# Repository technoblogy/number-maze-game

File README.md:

# Number Maze Game
A handheld game that displays logic mazes you have to solve by pressing the buttons.

For the original version see: <http://www.technoblogy.com/show?45JT>.

For the updated version, with additional harder mazes, see: <http://www.technoblogy.com/show?48BN>.

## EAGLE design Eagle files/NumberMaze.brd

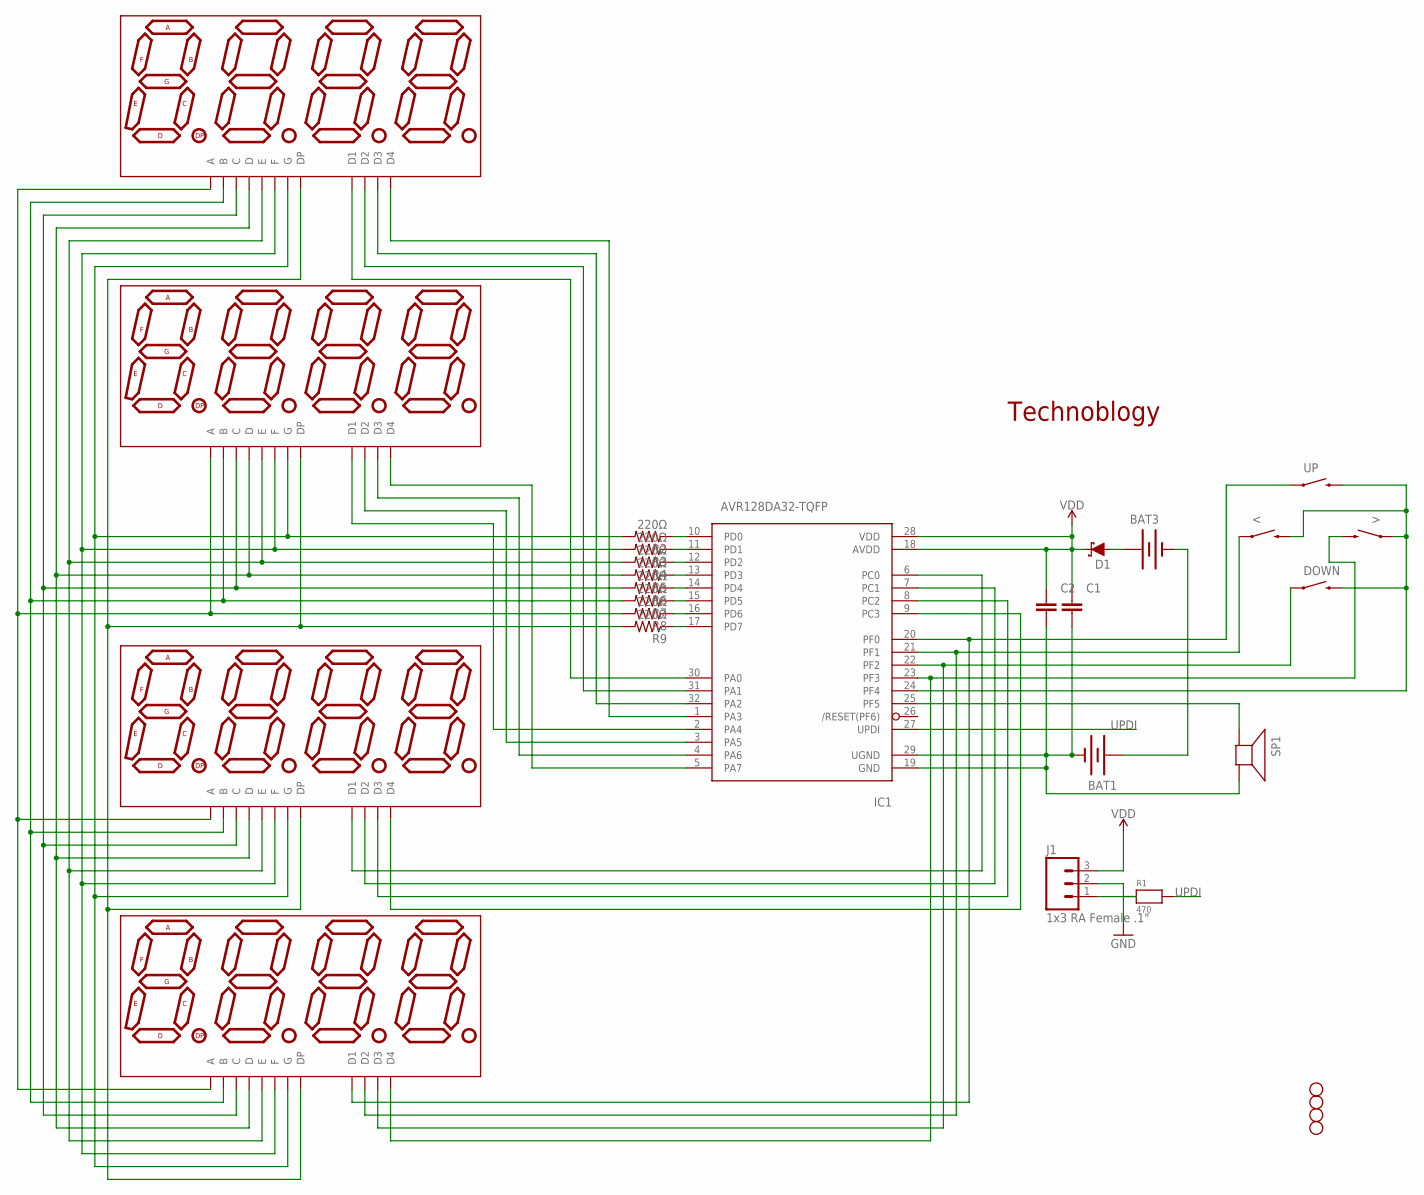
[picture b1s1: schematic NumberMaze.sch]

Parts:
<: SWITCH-MOMENTARY-2PTH; TACTILE-PTH
>: SWITCH-MOMENTARY-2PTH; TACTILE-PTH
BAT1, BAT3: BATTERYAA-KIT; BATTERY-AA-KIT
C1, C2: 100n; 0805
D1: 3A/10V/280mV; SOD-323
DISP1, DISP2, DISP3, DISP4: KYX-2381
DOWN: SWITCH-MOMENTARY-2PTH; TACTILE-PTH
IC1: AVR128DA32-TQFP; TQFP32-08
J1: 1x3 RA Female .1"; 1X03_SMD_RA_FEMALE
JP1, JP2, JP4, JP5: STAND-OFF
R1: 470; _0805MP
R2, R3, R4, R5, R6, R7, R8, R9: 220Ω; 0805
SP1: SPEAKER/AL60P; AL60P
UP: SWITCH-MOMENTARY-2PTH; TACTILE-PTH

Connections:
GND: BAT1.GND@1 (-), C1.2, C2.2, IC1.19 (GND), IC1.29 (UGND), J1.2, SP1.2 (-)
unnamed: DISP1.11 (A), DISP2.11 (A), DISP3.11 (A), DISP4.11 (A), R8.2
unnamed: DISP1.7 (B), DISP2.7 (B), DISP3.7 (B), DISP4.7 (B), R7.2
unnamed: DISP1.4 (C), DISP2.4 (C), DISP3.4 (C), DISP4.4 (C), R6.2
unnamed: DISP1.2 (D), DISP2.2 (D), DISP3.2 (D), DISP4.2 (D), R5.2
unnamed: DISP1.1 (E), DISP2.1 (E), DISP3.1 (E), DISP4.1 (E), R4.2
unnamed: DISP1.10 (F), DISP2.10 (F), DISP3.10 (F), DISP4.10 (F), R3.2
unnamed: DISP1.5 (G), DISP2.5 (G), DISP3.5 (G), DISP4.5 (G), R2.2
unnamed: DISP1.3 (DP), DISP2.3 (DP), DISP3.3 (DP), DISP4.3 (DP), R9.2
unnamed: IC1.17 (PD7), R9.1
unnamed: IC1.16 (PD6), R8.1
unnamed: IC1.15 (PD5), R7.1
unnamed: IC1.14 (PD4), R6.1
unnamed: IC1.13 (PD3), R5.1
unnamed: IC1.12 (PD2), R4.1
unnamed: IC1.11 (PD1), R3.1
unnamed: IC1.10 (PD0), R2.1
unnamed: BAT3.PWR@1 (+), D1.A
unnamed: IC1.25 (PF5), SP1.1 (+)
unnamed: DISP3.9 (D2), IC1.7 (PC1)
unnamed: BAT1.PWR@1 (+), BAT3.GND@1 (-)
unnamed: DISP1.6 (D4), IC1.1 (PA3)
unnamed: DISP3.6 (D4), IC1.9 (PC3)
unnamed: DISP1.12 (D1), IC1.30 (PA0)
unnamed: DISP1.9 (D2), IC1.31 (PA1)
unnamed: DISP1.8 (D3), IC1.32 (PA2)
unnamed: <.3 (2), >.1, DOWN.3 (2), IC1.24 (PF4), UP.3 (2)
unnamed: DISP2.6 (D4), IC1.5 (PA7)
unnamed: DISP2.8 (D3), IC1.4 (PA6)
unnamed: DISP4.12 (D1), IC1.20 (PF0), UP.1
unnamed: <.1, DISP4.9 (D2), IC1.21 (PF1)
unnamed: DISP4.8 (D3), DOWN.1, IC1.22 (PF2)
unnamed: >.3 (2), DISP4.6 (D4), IC1.23 (PF3)
unnamed: DISP3.8 (D3), IC1.8 (PC2)
unnamed: J1.1, R1.1
unnamed: DISP3.12 (D1), IC1.6 (PC0)
unnamed: DISP2.9 (D2), IC1.3 (PA5)
unnamed: DISP2.12 (D1), IC1.2 (PA4)
UPDI: IC1.27 (UPDI), R1.2
VDD: C1.1, C2.1, D1.C, IC1.18 (AVDD), IC1.28 (VDD), J1.3

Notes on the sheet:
Technoblogy

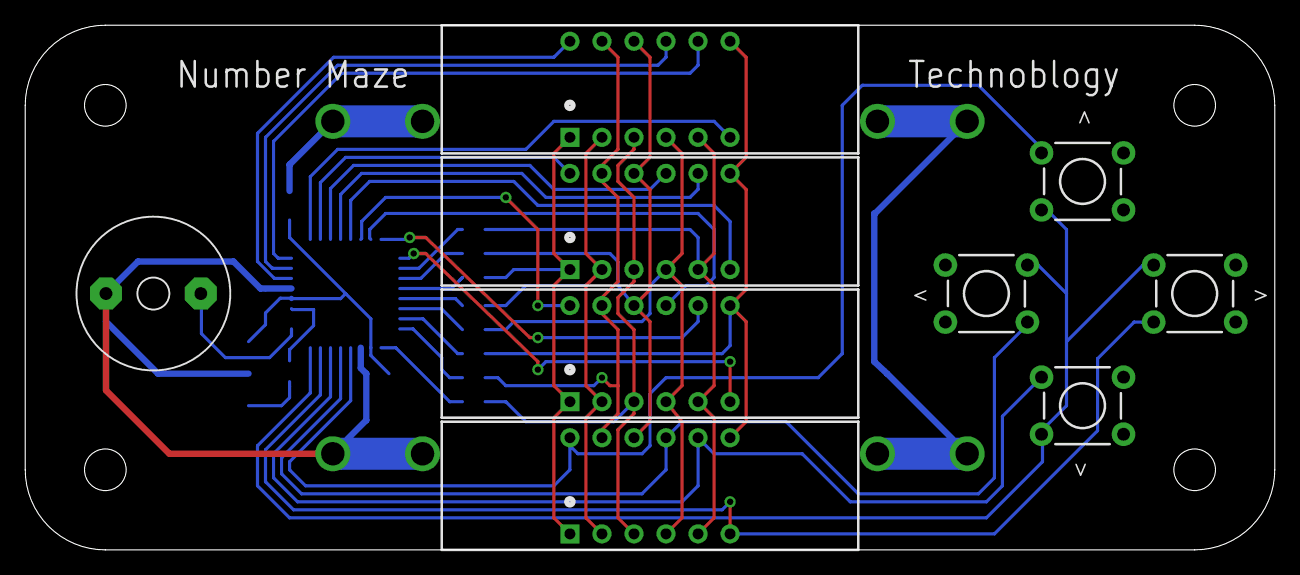
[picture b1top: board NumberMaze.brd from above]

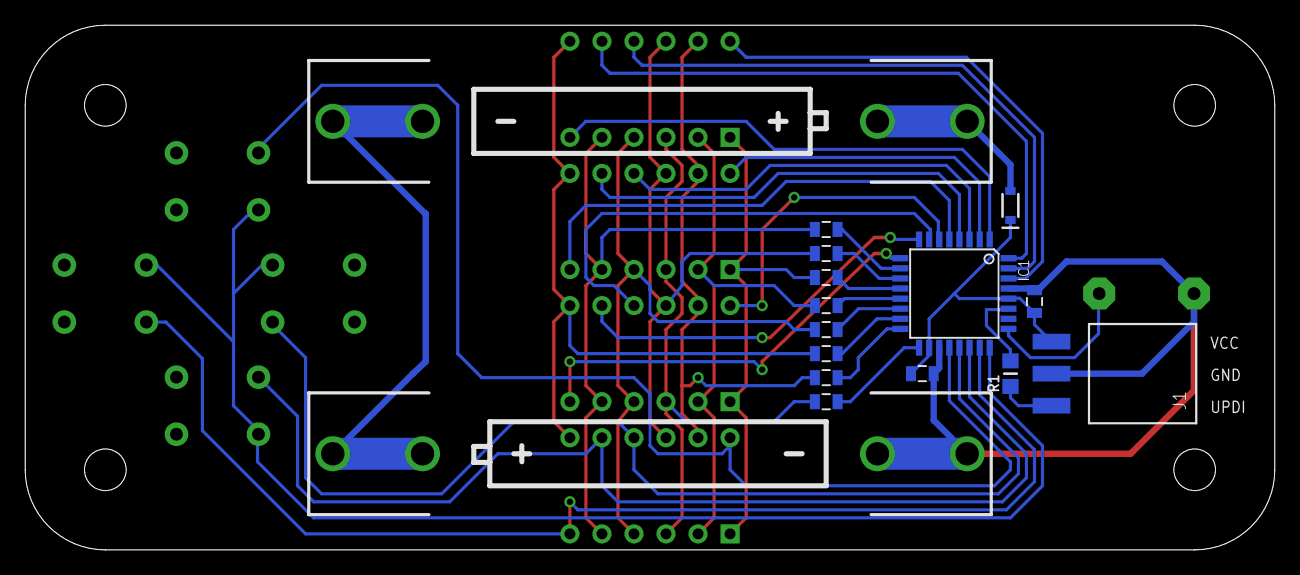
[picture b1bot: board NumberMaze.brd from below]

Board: 2 copper layers, 99.1 x 41.6 mm, 29 parts (16 on the bottom side), 40 nets.

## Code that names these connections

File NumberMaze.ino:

/* Number Maze Game - see http://www.technoblogy.com/show?45JT

   David Johnson-Davies - www.technoblogy.com - 21st December 2022
   AVR128DA32 or ATmega4808 @ 4 MHz (internal oscillator; BOD disabled)
   
   CC BY 4.0
   Licensed under a Creative Commons Attribution 4.0 International license: 
   http://creativecommons.org/licenses/by/4.0/
*/

#include <avr/sleep.h>

#if defined(__AVR_ATmegax08__)
#define TCB_CLKSEL_DIV1_gc TCB_CLKSEL_CLKDIV1_gc
#endif

// Seven segment displays

// Cathodes, Arduino pin numbers
uint8_t cathode[16] = { 0, 1, 2, 3, 4, 5, 6, 7, 8, 9, 10, 11, 20, 21, 22, 23 };

// Translation tables
uint8_t symbol[]  = { '0',  '1',  '2',  '3',  '4',  '5',  '6',  '7',  '8',  '9',  
                      ' ',  'H',  'P', 'L',  'A',  'Y',   'n',  'o',  0xff };
uint8_t segment[] = { 0x7e, 0x30, 0x6d, 0x79, 0x33, 0x5b, 0x5f, 0x70, 0x7f, 0x7b,
                      0x00, 0x37, 0x67, 0x0e, 0x77, 0x3b, 0x15, 0x1d, 0xff };

// Mazes
const int TotalMazes = 12;

uint8_t mazes[TotalMazes][17] = {
  "201111232221212H", // 7 8+5
  "3212122112H21213", // 7 7+4
  "121213122132213H", // 8 9+3
  "221121112222111H", // 8 9b+3
  "131212131131232H", // 9 9+2
  "112213123122112H", // 9 10+4
  "1313213221H22332", // 10 8+3
  "231111333113332H", // 10 9+0
  "3131221212H33133", // 10 9+2
  "222231131321112H", // 10 10+1
  "223121212121112H", // 11 8+3
  "212331013310132H"  // 11 8b+0
};

// Number of steps in each maze
uint8_t steps[TotalMazes] = { 7, 7, 8, 8, 9, 9, 10, 10, 10, 10, 11, 11 }; 

// Intro screen
uint8_t intro[17] = { "    PLAYno 1    " };

// Globals
int Maze = 0;
uint8_t *Buffer = intro;
volatile uint8_t Sound = 0;
enum sounds { NONE, HORIZONTAL, VERTICAL, UNDO, SOLVED };
volatile uint8_t Player = 16;

// Buttons **********************************************

void SetupButtons () {
  PORTF.PIN4CTRL = PORT_PULLUPEN_bm;                       // PF4 input pullup
}

ISR(PORTF_PORT_vect) {
  PORTF.INTFLAGS = PIN4_bm;                                // Clear the interrupt flag
}

// Display multiplexer **********************************************

const int UndoBuffer = 100;
const unsigned long Timeout = 60000;                       // 1 minute
volatile unsigned long Start;

void SetupDisplay () {
  // Cathodes input low
  PORTA.DIRCLR = 0xff; PORTA.OUTCLR = 0xff;                // PA0 to PA7
  PORTC.DIRCLR = 0x0f; PORTC.OUTCLR = 0x0f;                // PC0 to PC3
  PORTF.DIRCLR = 0x0f; PORTF.OUTCLR = 0x0f;                // PF0 to PF3
  // Anodes output low
  PORTD.DIRSET = 0xff; PORTD.OUTCLR = 0xff;                // PD0 to PD7
  // Set up Timer/Counter TCB to multiplex the display
  TCB0.CCMP = 2499;                                        // 4MHz/2500 = 1600Hz
  TCB0.CTRLA = TCB_CLKSEL_DIV1_gc | TCB_ENABLE_bm;         // Divide timer by 1
  TCB0.CTRLB = 0;                                          // Periodic Interrupt
  TCB0.INTCTRL = TCB_CAPT_bm;                              // Enable interrupt
}

// Timer/Counter TCB interrupt - multiplexes the display
ISR(TCB0_INT_vect) {
  TCB0.INTFLAGS = TCB_CAPT_bm;                             // Clear the interrupt flag
  DisplayNextDigit();
}

uint8_t Segments (uint8_t c) {
  int p = 0;
  while (symbol[p] != 0xff) {
    if (symbol[p] == c) return segment[p];
    p++;
  }
  return 0;
}

void NextLevel (uint8_t press) {
  if (press - 12 == 1) Maze = 0;                           // Left button resets to 1
  else Maze = (Maze + 1) % TotalMazes;                     // Wrap around
  Buffer = intro;
  Buffer[11] = (Maze+1)%10 + '0';
  int tens = (Maze+1)/10;
  if (tens == 0) Buffer[10] = ' '; else Buffer[10] = tens + '0';
  Player = 16;                                             // Go to Intro screen
}

void HandleButtons (uint8_t digit) {
  static uint8_t press = 0, last = 0, count = 0, move = 0;
  static uint8_t undo[UndoBuffer];
  if (digit >= 12 && digitalRead(24) == 0) { 
    press = digit;
    count++;
  }
  if (digit == 15) {
    if (count > 100) {                                     // Long press 1 second
      // Long press = undo
      if (move > 0) {
        move--;
        Player = undo[move];
        Sound = Sound | 1<<UNDO;
      }
      count = 0;
    } else if (press != 0 && press != last) {
      if (Player == 16) {                                  // Intro screen
        // Start new maze
        Player = 0; Buffer = mazes[Maze]; move = 0;
      } else if (mazes[Maze][Player] == 'H') {             // Player on Home
        // Proceed after finishing a level
        NextLevel(press);
      } else {
        // Move player
        int dir = press-12; // Up = 0, Left = 1, Down = 2, Right = 3
        int cell = mazes[Maze][Player];
        int mex = Player & 0x03, mey = Player>>2;
        int nex = mex + (dir%2) * (dir-2) * (cell-'0');
        int ney = mey + (1-dir%2) * (dir-1) * (cell-'0');
        if (nex != mex && nex >= 0 && nex <= 3) {          // Move horizontally
          mex = nex; Sound = Sound | 1<<HORIZONTAL;
          undo[move] = Player; if (move < UndoBuffer-1) move++;
        } else if (ney != mey && ney >= 0 && ney <= 3) {   // Move vertically
          mey = ney; Sound = Sound | 1<<VERTICAL;
          undo[move] = Player; if (move < UndoBuffer-1) move++;
        }
        Player = mey<<2 | mex;
        // Moved onto Home
        if (mazes[Maze][Player] == 'H') Sound = Sound | 1<<SOLVED;
        count = 0;
      }
    }
    last = press;
    press = 0;
  }
}
  
void DisplayNextDigit() {
  static uint8_t digit = 0;
  pinMode(cathode[digit], INPUT);
  digit = (digit + 1) & 0xF;
  uint8_t bits = Segments(Buffer[digit]);
  if (digit == Player) bits = bits + 0x80;                 // Decimal point
  PORTD.OUT = bits;
  pinMode(cathode[digit], OUTPUT);
  HandleButtons(digit);
}

// Play notes **********************************************

uint8_t scale[] = {239,226,213,201,190,179,169,160,151,142,134,127};

// Note on WO5
void SetupNote () {
  PORTF.DIRSET = PIN5_bm;                                  // PF5 as output
  PORTMUX.TCAROUTEA = PORTMUX_TCA0_PORTF_gc;               // PWM on port F
  TCA0.SINGLE.CTRLD = TCA_SINGLE_SPLITM_bm;
  TCA0.SPLIT.CTRLA = TCA_SPLIT_ENABLE_bm | 5<<TCA_SPLIT_CLKSEL_gp; // DIV64
  TCA0.SPLIT.CTRLB = TCA_SPLIT_HCMP2EN_bm;                 // Note on WO5 = PF5
  TCA0.SPLIT.HCMP2 = 0;
}

void PlayNote (int note, int millis) {
  TCA0.SPLIT.HPER = scale[note];
  TCA0.SPLIT.HCMP2 = scale[note]>>1;
  delay(millis);
  TCA0.SPLIT.HCMP2 = 0;
}

boolean PlaySound (int sound) {
  if (Sound & 1<<sound) {
    Sound = Sound & ~(1<<sound);
    Start = millis();
    return true;
  } else return false;
}

// Setup **********************************************

void setup () {
  set_sleep_mode(SLEEP_MODE_PWR_DOWN);
  SetupDisplay();
  SetupButtons();
  SetupNote();
  ADC0.CTRLA = 0; // Disable ADC to save power
  Start = millis();
}

// Play sounds
void loop () {
  if (PlaySound(HORIZONTAL)) PlayNote(9,200);
  if (PlaySound(VERTICAL)) PlayNote(11, 200);
  if (PlaySound(UNDO)) PlayNote(7, 200);
  if (PlaySound(SOLVED)) {
    delay(250); PlayNote(4, 250); PlayNote(5, 250);
    PlayNote(7, 250); PlayNote(9, 250); PlayNote(11, 750); 
  }
  // Go to sleep?
  if ((unsigned long)(millis() - Start) > Timeout) {
    TCB0.CTRLA = 0;                                        // Turn off display multiplexing
    PORTA.DIRSET = 0xff;                                   // Display cathodes to outputs
    PORTC.DIRSET = 0x0f;
    PORTF.DIRSET = 0x0f;
    PORTD.OUTCLR = 0xff;                                   // Display anodes output low
    PORTF.PIN4CTRL = PORT_PULLUPEN_bm | PORT_ISC_LEVEL_gc; // PF4 input pullup with interrupt
    sleep_enable();
    sleep_cpu();
    PORTF.PIN4CTRL = PORT_PULLUPEN_bm;                     // Turn off PF4 interrupt
    while (digitalRead(24) == 0);                          // Wait for key released
    PORTA.DIRCLR = 0xff;                                   // Display cathodes back to inputs
    PORTC.DIRCLR = 0x0f;
    PORTF.DIRCLR = 0x0f;
    TCB0.CTRLA = TCB_CLKSEL_DIV1_gc | TCB_ENABLE_bm;       // Turn on display multiplexing
    Start = millis();
  }
}

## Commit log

2022-12-22 Version 1 - 21st December 2022
2023-02-14 Version 2 - 14th February 2023

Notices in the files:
parts and their libraries:
SparkFun-Electromechanical: Licensing: Creative Commons ShareAlike 4.0 International - https://creativecommons.org/licenses/by-sa/4.0
microbuilder: This work is placed in the public domain, and may be freely used for commercial and non-commercial work with the following conditions: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
